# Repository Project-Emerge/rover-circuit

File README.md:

# Dropbot Circuit Board

## Scope of the Board

The Rover Circuit is a comprehensive controller board designed for robotics applications, specifically targeted at robot rovers. A key goal of this project is to make swarm robotics accessible to students, educators, and researchers, providing an affordable and easy-to-use platform for experimenting with multi-agent systems and decentralized control. 

It integrates dual-motor driving capabilities, 2-cell Li-ion battery management with USB-C charging, and provides multiple power domains (3.3V, 5V, 6V) for logic, sensors, and external compute modules like a Raspberry Pi. The board includes I2C and GPIO interfaces to facilitate communication with various sensors and control systems, making it a compact, all-in-one hardware platform for mobile robot development.

## Main Components & Features

* **Espressif ESP32-C6 (Microcontroller)**: The core processing unit of the board, offering Wi-Fi 6, Bluetooth LE, and IEEE 802.15.4 (Zigbee/Thread) connectivity. Its robust wireless capabilities are ideal for inter-robot communication in a swarm network.
* **Decawave DWM1000 (UWB Module)**: An Ultra-Wideband transceiver module designed for precise indoor localization, spatial awareness, and ranging between rovers. Crucial for coordinated swarm movements and mapping.
* **9-DOF Inertial Measurement Unit (IMU)**: 
  * *Bosch BMI270*: A 6-axis accelerometer and gyroscope for tracking movement and rotation.
  * *MEMSIC MMC5983MA*: A high-precision 3-axis magnetometer acting as a digital compass for absolute heading orientation.
* **TI BQ25887 (Battery Management)**: A 2-cell Li-ion boost-mode battery charger with integrated cell balancing and USB-C input support. It handles safe charging and power management for the entire rover.
* **TI DRV8833 (Motor Driver)**: A dual H-bridge motor driver capable of delivering 1.5A RMS per bridge. It is used to independently drive two DC motors (such as N20 motors) for locomotion.
* **STM6601 (Power Controller)**: A smart push-button on/off controller for robust hardware power management and user interaction.
* **Power Distribution System**: Dedicated voltage regulators generating 3.3V for internal logic and sensors, 6V for the motors, and a clean 5V output.
* **SBC Expansion & User Interface**: An expansion header capable of powering and interfacing with a Single Board Computer (e.g., Raspberry Pi) over 5V, along with a dedicated I2C connector for attaching an OLED display module.

These components work together to provide a complete, robust sensing, processing, and locomotion backend, allowing developers to focus on high-level swarm robotics software and decentralized algorithms without worrying about hardware integration.

## Sponsors

---

## License

MIT License - see LICENSE file for details.

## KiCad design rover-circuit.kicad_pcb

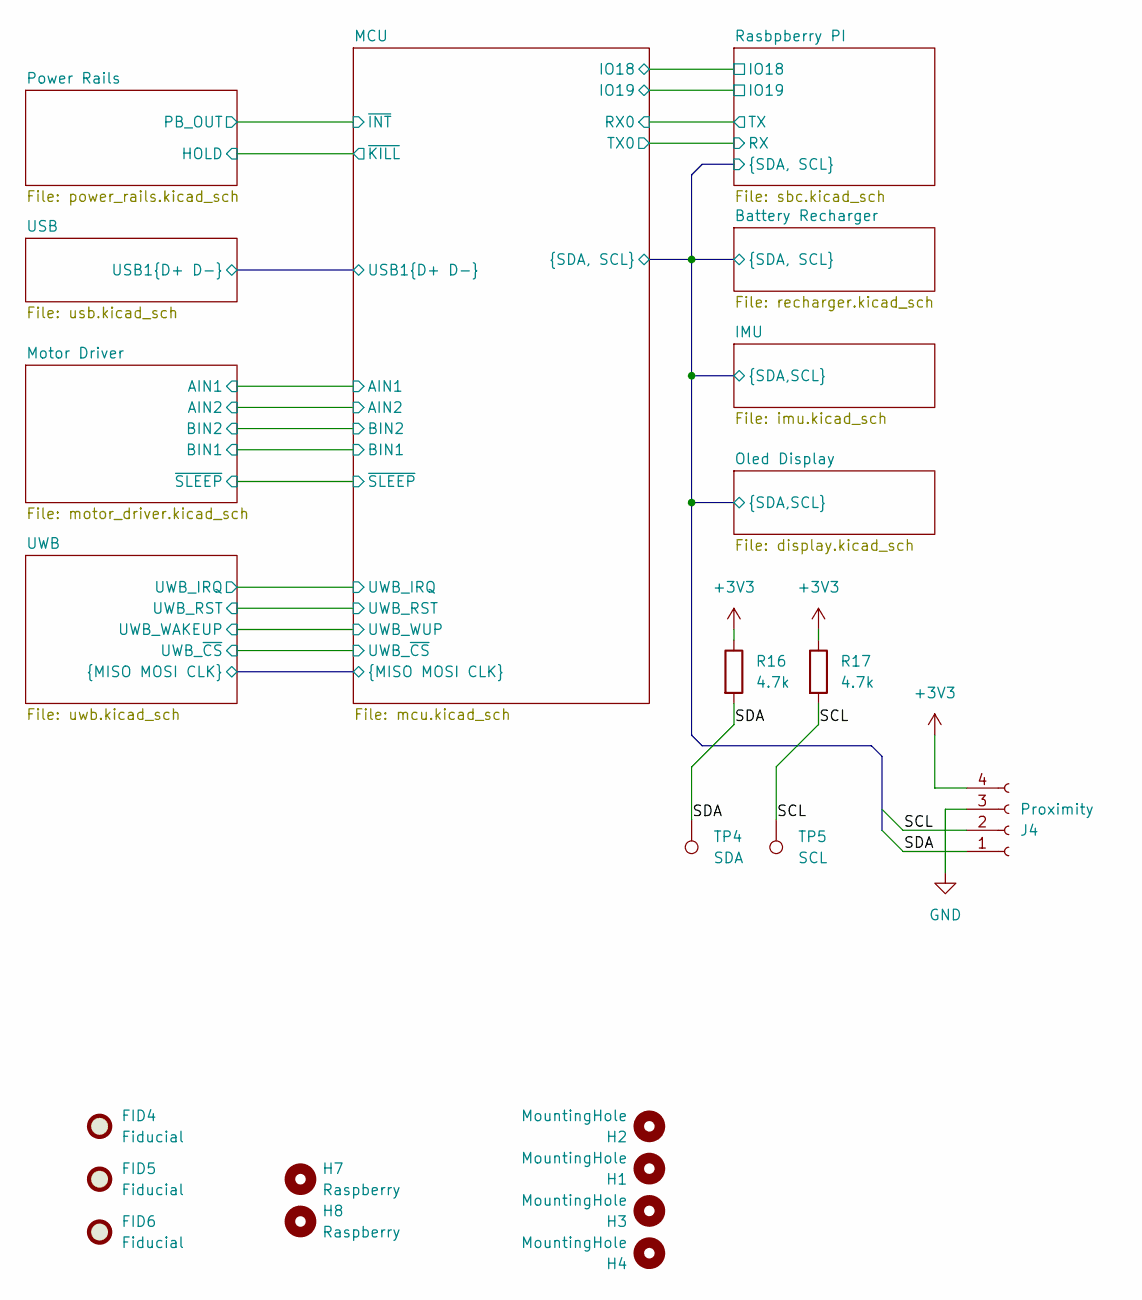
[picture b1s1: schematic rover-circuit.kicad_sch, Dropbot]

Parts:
FID4, FID5, FID6: Fiducial; Fiducial_0.5mm_Mask1mm
H1, H2, H3, H4: MountingHole; MountingHole_2.2mm_M2
H7, H8: Raspberry; MountingHole_2.5mm
J4: Proximity; JST_PH_S4B-PH-SM4-TB_1x04-1MP_P2.00mm_Horizontal; MPN S4B-PH-SM4-TB(LF)(SN); LCSC C265102
R16, R17: 4.7k; R_0603_1608Metric; MPN GPR060347; LCSC C25999
TP4: SDA; TestPoint_Pad_D1.0mm
TP5: SCL; TestPoint_Pad_D1.0mm

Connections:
+3V3: J4.4, R16.1, R17.1; also elsewhere on the board
/Battery Recharger/SCL: J4.2, R17.2, TP5.1 (1_1); also elsewhere on the board
/Battery Recharger/SDA: J4.1, R16.2, TP4.1 (1_1); also elsewhere on the board
GND: J4.3; also elsewhere on the board

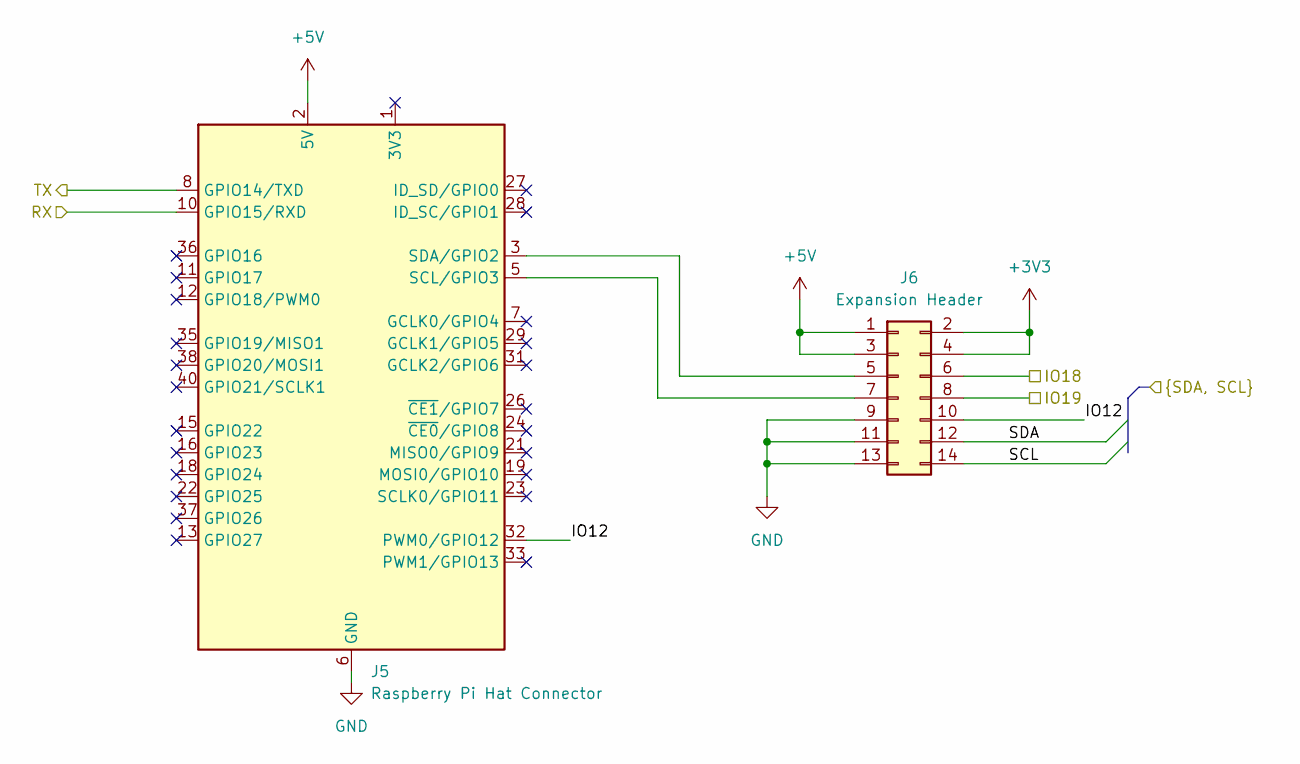
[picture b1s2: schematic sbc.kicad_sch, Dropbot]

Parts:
J5: Raspberry Pi Hat Connector; PinSocket_2x20_P2.54mm_Vertical_SMD; MPN 953240-2000-AR-PR; LCSC C22436166
J6: Expansion Header; PinHeader_2x07_P2.54mm_Vertical; MPN 61201421621; LCSC C492424

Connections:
+3V3: J6.2, J6.4; also elsewhere on the board
+5V: J5.2 (5V), J5.4 (5V), J6.1, J6.3; also elsewhere on the board
/Battery Recharger/SCL: J6.14; also elsewhere on the board
/Battery Recharger/SDA: J6.12; also elsewhere on the board
/MCU/IO18: J6.6; also elsewhere on the board
/MCU/IO19: J6.8; also elsewhere on the board
/MCU/RX0: J5.8 (GPIO14/TXD); also elsewhere on the board
/MCU/TX0: J5.10 (GPIO15/RXD); also elsewhere on the board
/Rasbpberry PI/IO12: J5.32 (PWM0/GPIO12), J6.10
GND: J5.6 (GND), J5.9 (GND), J5.14 (GND), J5.20 (GND), J5.25 (GND), J5.30 (GND), J5.34 (GND), J5.39 (GND), J6.9, J6.11, J6.13; also elsewhere on the board
unnamed: J5.5 (SCL/GPIO3), J6.7
unnamed: J5.3 (SDA/GPIO2), J6.5

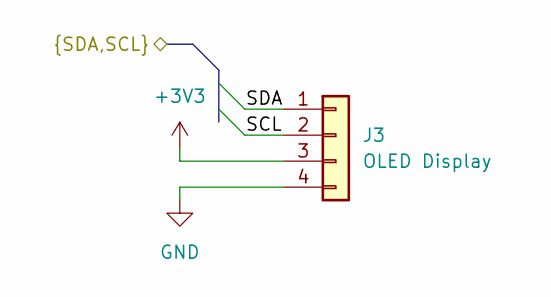
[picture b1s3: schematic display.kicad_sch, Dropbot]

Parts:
J3: OLED Display; PinSocket_1x04_P2.54mm_Vertical; MPN PPTC041LFBN-RC; LCSC C2718488

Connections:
+3V3: J3.3; also elsewhere on the board
/Battery Recharger/SCL: J3.2; also elsewhere on the board
/Battery Recharger/SDA: J3.1; also elsewhere on the board
GND: J3.4; also elsewhere on the board

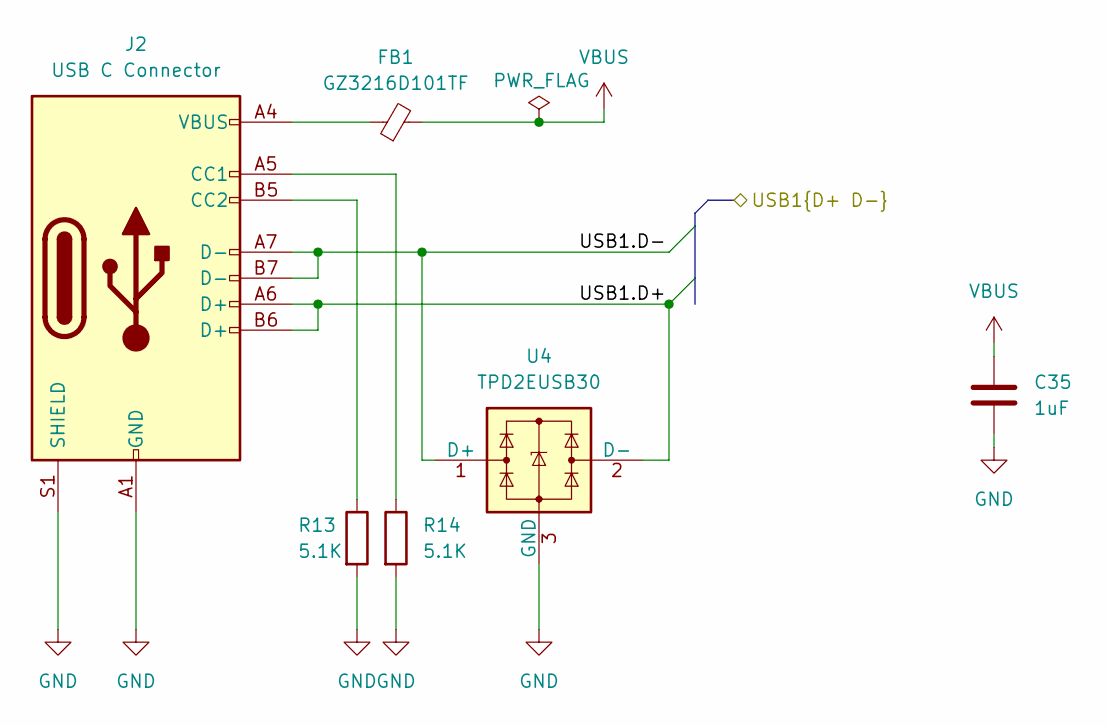
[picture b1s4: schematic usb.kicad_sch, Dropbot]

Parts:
C35: 1uF; C_0603_1608Metric; MPN GPC0603105; LCSC C5673
FB1: GZ3216D101TF; L_1206_3216Metric; MPN BLM31PG500SN1L; LCSC C369799
J2: USB C Connector; USB_C_Receptacle_G-Switch_GT-USB-7010ASV; MPN GT-USB-7010ASV; LCSC C2988369
R13, R14: 5.1K; R_0402_1005Metric; MPN GPR040251; LCSC C25905
U4: TPD2EUSB30; Texas_DRT-3; MPN TPD2EUSB30ADRTR; LCSC C94934

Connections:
/MCU/USB1.D+: J2.A6 (D+), J2.B6 (D+), U4.2 (D-); also elsewhere on the board
/MCU/USB1.D-: J2.A7 (D-), J2.B7 (D-), U4.1 (D+); also elsewhere on the board
GND: C35.2, J2.A1 (GND), J2.A12 (GND), J2.B1 (GND), J2.B12 (GND), J2.S1 (SHIELD), R13.2, R14.2, U4.3 (GND); also elsewhere on the board
unnamed: FB1.1, J2.A4 (VBUS), J2.A9 (VBUS), J2.B4 (VBUS), J2.B9 (VBUS)
unnamed: J2.A5 (CC1), R14.1
unnamed: J2.B5 (CC2), R13.1
VBUS: C35.1, FB1.2; also elsewhere on the board

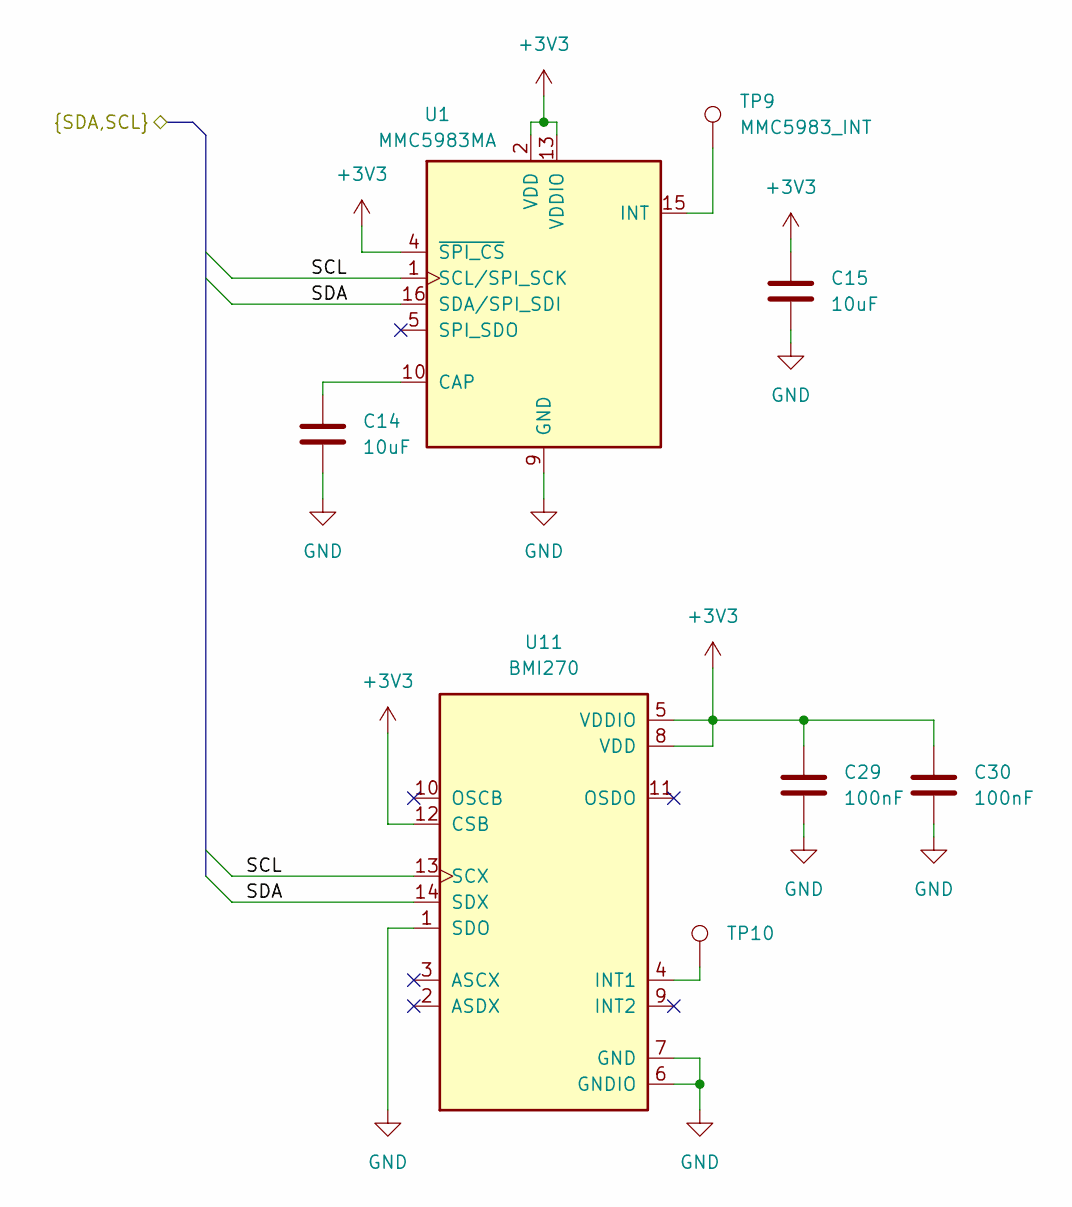
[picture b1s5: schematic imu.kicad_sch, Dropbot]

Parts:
C14, C15: 10uF; C_0603_1608Metric; MPN GPC0603106; LCSC C962136
C29, C30: 100nF; C_0603_1608Metric; MPN GPC0603104; LCSC C14663
TP9: MMC5983_INT; TestPoint_Pad_D1.0mm
TP10: INT1; TestPoint_Pad_D1.0mm
U1: MMC5983MA; LGA-16_3x3mm_P0.5mm; PARTREV A; LCSC C404329
U11: BMI270; Bosch_LGA-14_3x2.5mm_P0.5mm; MPN BMI270; LCSC C2836813

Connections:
+3V3: C15.1, C29.1, C30.1, U1.2 (VDD), U1.4 (~SPI_CS), U1.13 (VDDIO), U11.5 (VDDIO), U11.8 (VDD), U11.12 (CSB); also elsewhere on the board
/Battery Recharger/SCL: U1.1 (SCL/SPI_SCK), U11.13 (SCX); also elsewhere on the board
/Battery Recharger/SDA: U1.16 (SDA/SPI_SDI), U11.14 (SDX); also elsewhere on the board
GND: C14.2, C15.2, C29.2, C30.2, U1.9 (GND), U1.11 (GND), U11.1 (SDO), U11.6 (GNDIO), U11.7 (GND); also elsewhere on the board
unnamed: C14.1, U1.10 (CAP)
unnamed: TP9.1 (1_1), U1.15 (INT)
unnamed: TP10.1 (1_1), U11.4 (INT1)

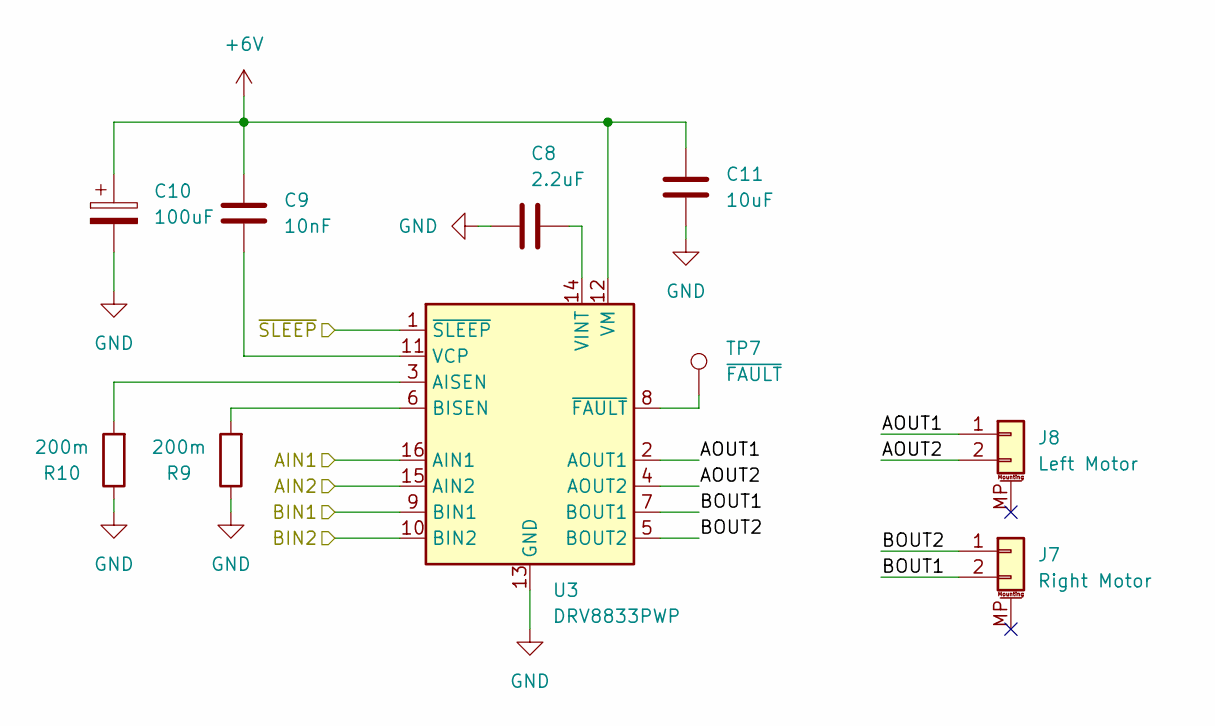
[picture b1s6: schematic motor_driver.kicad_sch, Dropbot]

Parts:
C8: 2.2uF; C_0603_1608Metric; MPN GPC0603225; LCSC C23630
C9: 10nF; C_0603_1608Metric; MPN GPC0603103; LCSC C1589
C10: 100uF; CP_Elec_6.3x5.4; MPN EEE-1CA101SP; LCSC C2887276
C11: 10uF; C_0805_2012Metric; MPN GPC0805106; LCSC C326595
J7: Right Motor; JST_PH_S2B-PH-SM4-TB_1x02-1MP_P2.00mm_Horizontal; MPN S2B-PH-SM4-TB(LF)(SN); LCSC C295747
J8: Left Motor; JST_PH_S2B-PH-SM4-TB_1x02-1MP_P2.00mm_Horizontal; MPN S2B-PH-SM4-TB(LF)(SN); LCSC C295747
R9, R10: 200m; R_1206_3216Metric; MPN ERJ-8BWFR200V; LCSC C5127778
TP7: ~{FAULT}; TestPoint_Pad_D1.0mm
U3: DRV8833PWP; HTSSOP-16-1EP_4.4x5mm_P0.65mm_EP3.4x5mm_Mask2.46x2.31mm_The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; MPN DRV8833PWPR; LCSC C50506

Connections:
+6V: C9.1, C10.1, C11.1, U3.12 (VM); also elsewhere on the board
/MCU/AIN1: U3.16 (AIN1); also elsewhere on the board
/MCU/AIN2: U3.15 (AIN2); also elsewhere on the board
/MCU/BIN1: U3.9 (BIN1); also elsewhere on the board
/MCU/BIN2: U3.10 (BIN2); also elsewhere on the board
/MCU/~SLEEP: U3.1 (~SLEEP); also elsewhere on the board
/Motor Driver/AOUT1: J8.1, U3.2 (AOUT1)
/Motor Driver/AOUT2: J8.2, U3.4 (AOUT2)
/Motor Driver/BOUT1: J7.2, U3.7 (BOUT1)
/Motor Driver/BOUT2: J7.1, U3.5 (BOUT2)
GND: C8.2, C10.2, C11.2, R9.1, R10.1, U3.13 (GND), U3.17 (GND); also elsewhere on the board
unnamed: R10.2, U3.3 (AISEN)
unnamed: R9.2, U3.6 (BISEN)
unnamed: C9.2, U3.11 (VCP)
unnamed: C8.1, U3.14 (VINT)
unnamed: TP7.1 (1_1), U3.8 (~FAULT)

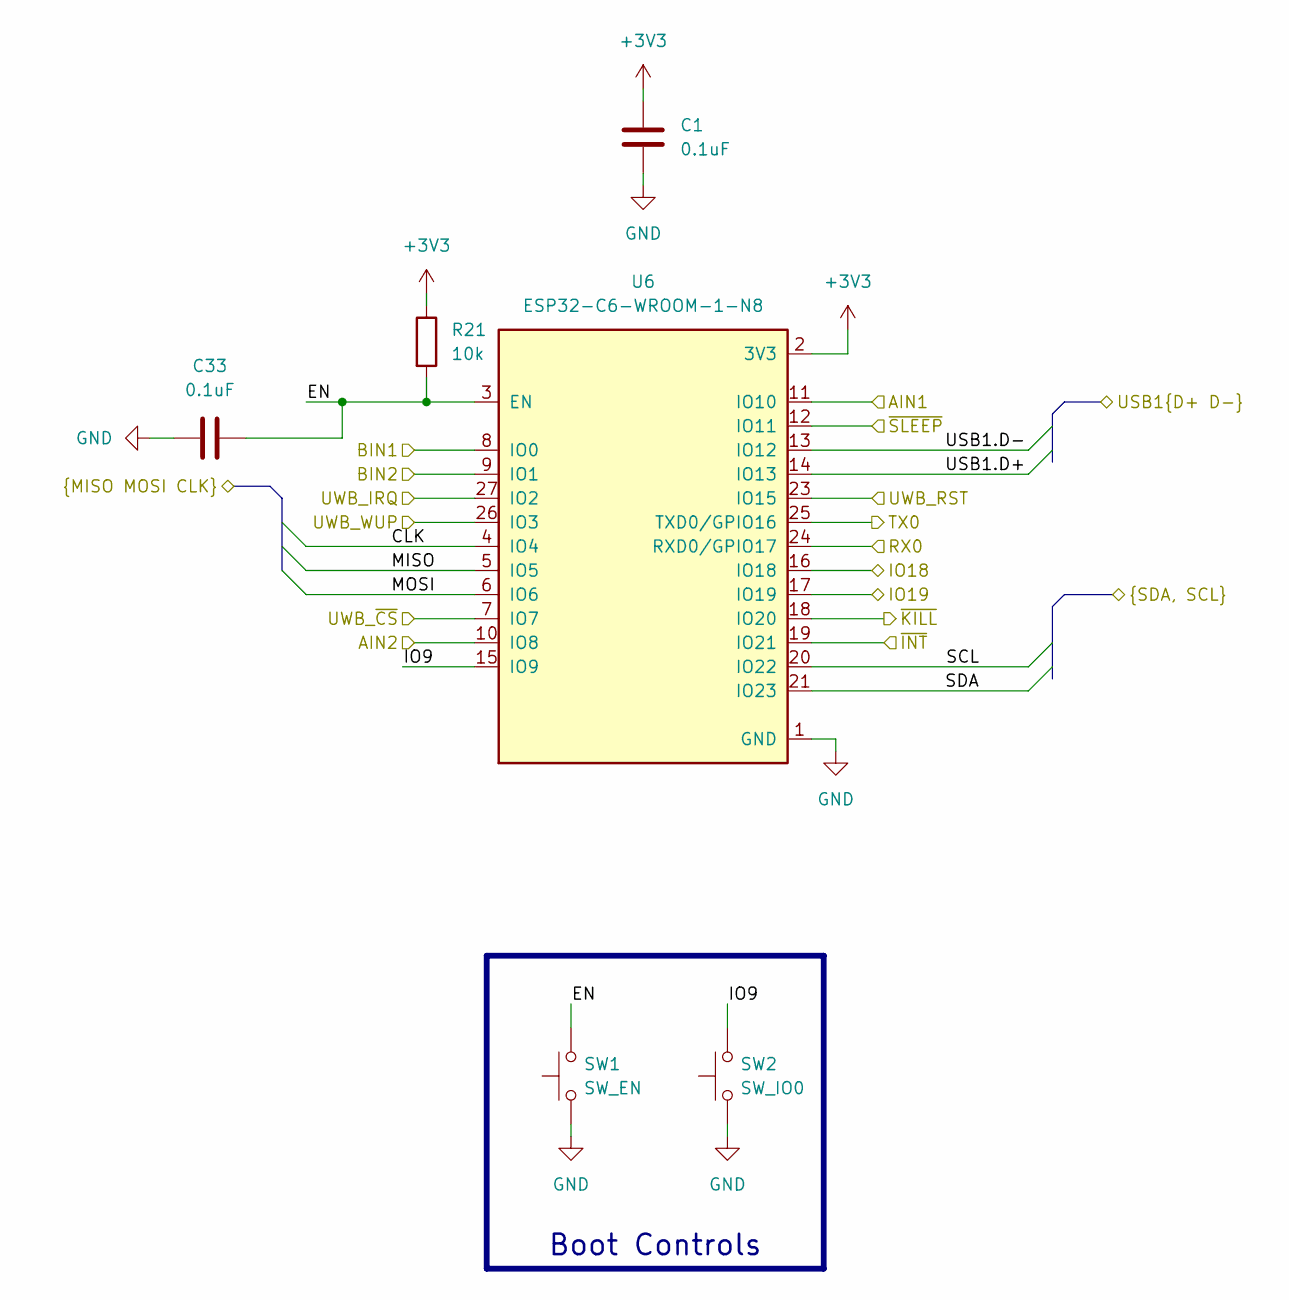
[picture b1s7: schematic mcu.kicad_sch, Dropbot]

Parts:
C1: 0.1uF; C_0805_2012Metric; LCSC C49678
C33: 0.1uF; C_0805_2012Metric; MPN GPC0805104; LCSC C49678
R21: 10k; R_0603_1608Metric; MPN GPR060310K; LCSC C15401
SW1: SW_EN; SW_SPST_B3U-1000P; MPN B3U-1000P; LCSC C231329
SW2: SW_IO0; SW_SPST_B3U-1000P; MPN B3U-1000P; LCSC C231329
U6: ESP32-C6-WROOM-1-N8; XCVR_ESP32-C6-WROOM-1-N8; PARTREV 1.0; LCSC C5366877

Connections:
+3V3: C1.1, R21.1, U6.2 (3V3); also elsewhere on the board
/Battery Recharger/SCL: U6.20 (IO22); also elsewhere on the board
/Battery Recharger/SDA: U6.21 (IO23); also elsewhere on the board
/MCU/AIN1: U6.11 (IO10); also elsewhere on the board
/MCU/AIN2: U6.10 (IO8); also elsewhere on the board
/MCU/BIN1: U6.8 (IO0); also elsewhere on the board
/MCU/BIN2: U6.9 (IO1); also elsewhere on the board
/MCU/CLK: U6.4 (IO4); also elsewhere on the board
/MCU/EN: C33.2, R21.2, SW1.2, U6.3 (EN)
/MCU/IO9: SW2.2, U6.15 (IO9)
/MCU/IO18: U6.16 (IO18); also elsewhere on the board
/MCU/IO19: U6.17 (IO19); also elsewhere on the board
/MCU/MISO: U6.5 (IO5); also elsewhere on the board
/MCU/MOSI: U6.6 (IO6); also elsewhere on the board
/MCU/RX0: U6.24 (RXD0/GPIO17); also elsewhere on the board
/MCU/TX0: U6.25 (TXD0/GPIO16); also elsewhere on the board
/MCU/USB1.D+: U6.14 (IO13); also elsewhere on the board
/MCU/USB1.D-: U6.13 (IO12); also elsewhere on the board
/MCU/UWB_IRQ: U6.27 (IO2); also elsewhere on the board
/MCU/UWB_RST: U6.23 (IO15); also elsewhere on the board
/MCU/UWB_WUP: U6.26 (IO3); also elsewhere on the board
/MCU/UWB_~CS: U6.7 (IO7); also elsewhere on the board
/MCU/~INT: U6.19 (IO21); also elsewhere on the board
/MCU/~KILL: U6.18 (IO20); also elsewhere on the board
/MCU/~SLEEP: U6.12 (IO11); also elsewhere on the board
GND: C1.2, C33.1, SW1.1, SW2.1, U6.1 (GND), U6.28 (GND), U6.29_1 (GND), U6.29_2 (GND), U6.29_3 (GND), U6.29_4 (GND), U6.29_5 (GND), U6.29_6 (GND), U6.29_7 (GND), U6.29_8 (GND), U6.29_9 (GND); also elsewhere on the board

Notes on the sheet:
Boot Controls

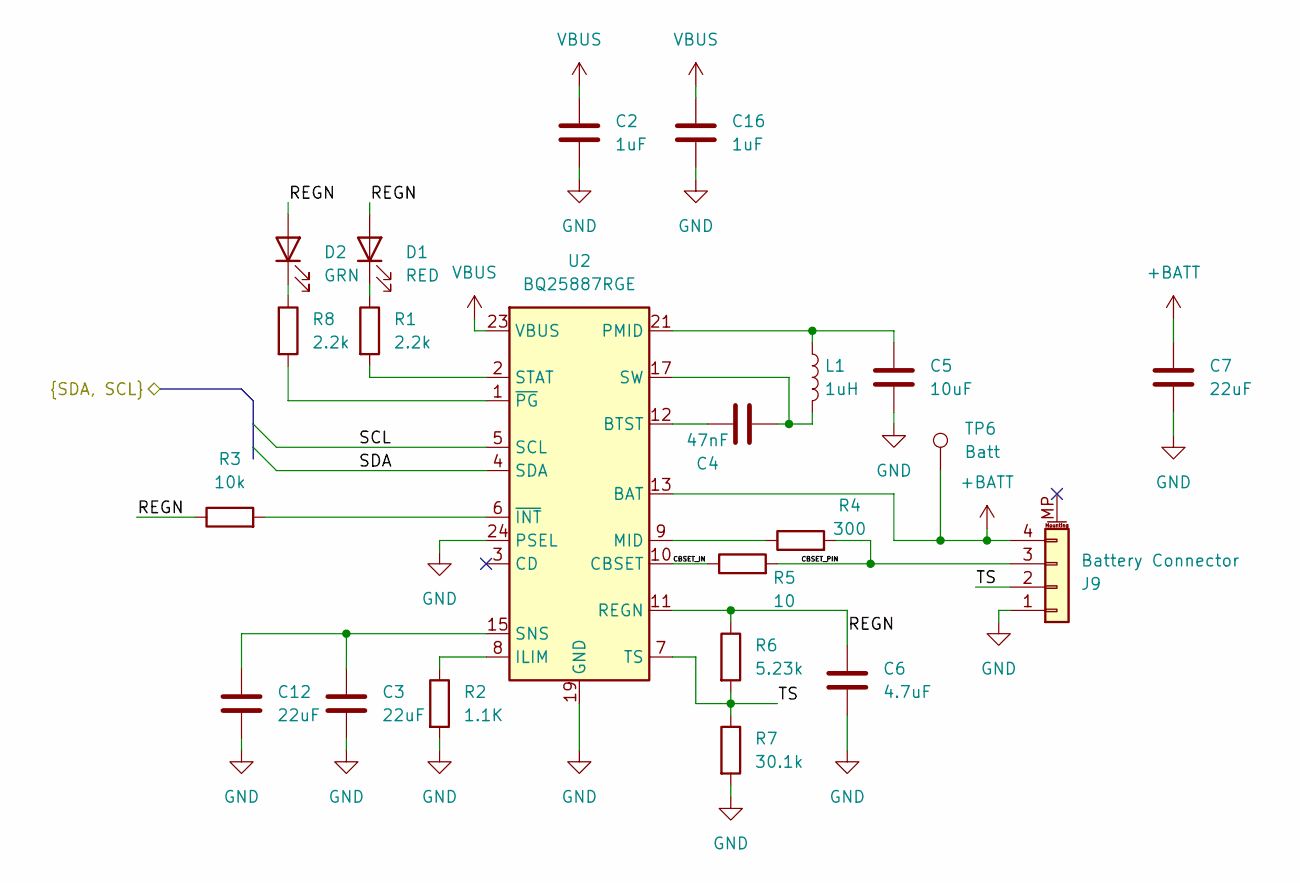
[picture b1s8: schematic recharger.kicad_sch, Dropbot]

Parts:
C2, C16: 1uF; C_0603_1608Metric; MPN GPC0603105; LCSC C5673
C3, C12: 22uF; C_1206_3216Metric; MPN GPC1206226; LCSC C53084537
C4: 47nF; C_0603_1608Metric; MPN GPC0603473; LCSC C1622
C5: 10uF; C_1206_3216Metric; MPN GPC1206106; LCSC C13585
C6: 4.7uF; C_0603_1608Metric; MPN GPC0603475; LCSC C69335
C7: 22uF; C_0603_1608Metric; MPN GRM188C61E226ME01D; LCSC C86295
D1: RED; LED_0603_1608Metric; MPN 150060RS75000; LCSC C2286
D2: GRN; LED_0603_1608Metric; MPN 150060VS75000; LCSC C965805
J9: Battery Connector; JST_PH_B4B-PH-SM4-TB_1x04-1MP_P2.00mm_Vertical; MPN B4B-PH-SM4-TB(LF)(SN); LCSC C160354
L1: 1uH; L_Sunlord_MWSA0518S; LCSC C475532
R1, R8: 2.2k; R_0603_1608Metric; MPN GPR060322; LCSC C4190
R2: 1.1K; R_0603_1608Metric; MPN GPR060311; LCSC C22764
R3: 10k; R_0603_1608Metric; MPN GPR060310K; LCSC C15401
R4: 300; R_0603_1608Metric; MPN GPR0603300R; LCSC C2930092
R5: 10; R_2512_6332Metric; MPN CRM2512-FX-10R0ELF; LCSC C840605
R6: 5.23k; R_0603_1608Metric; MPN GPR0603523; LCSC C23068
R7: 30.1k; R_0603_1608Metric; MPN GPR0603301; LCSC C23000
TP6: Batt; TestPoint_Pad_D1.0mm
U2: BQ25887RGE; Texas_RGE0024H_VQFN-24-1EP_4x4mm_P0.5mm_EP2.7x2.7mm; MPN BQ25887RGER; LCSC C2761614

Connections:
+BATT: C7.1, J9.4, TP6.1 (1_1), U2.13 (BAT), U2.14 (BAT); also elsewhere on the board
/Battery Recharger/CBSET_IN: R5.1, U2.10 (CBSET)
/Battery Recharger/CBSET_PIN: J9.3, R4.2, R5.2
/Battery Recharger/REGN: C6.1, D1.2 (A), D2.2 (A), R3.1, R6.1, U2.11 (REGN)
/Battery Recharger/SCL: U2.5 (SCL); also elsewhere on the board
/Battery Recharger/SDA: U2.4 (SDA); also elsewhere on the board
/Battery Recharger/TS: J9.2, R6.2, R7.1, U2.7 (TS)
GND: C2.2, C3.2, C5.2, C6.2, C7.2, C12.2, C16.2, J9.1, R2.2, R7.2, U2.19 (GND), U2.20 (GND), U2.24 (PSEL), U2.25 (GND); also elsewhere on the board
unnamed: C4.1, L1.2, U2.17 (SW), U2.18 (SW)
unnamed: C5.1, L1.1, U2.21 (PMID), U2.22 (PMID)
unnamed: C3.1, C12.1, U2.15 (SNS), U2.16 (SNS)
unnamed: D1.1 (K), R1.1
unnamed: D2.1 (K), R8.1
unnamed: C4.2, U2.12 (BTST)
unnamed: R2.1, U2.8 (ILIM)
unnamed: R4.1, U2.9 (MID)
unnamed: R1.2, U2.2 (STAT)
unnamed: R3.2, U2.6 (~INT)
unnamed: R8.2, U2.1 (~PG)
VBUS: C2.1, C16.1, U2.23 (VBUS); also elsewhere on the board

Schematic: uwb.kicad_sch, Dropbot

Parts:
C27: 0.1uF; C_0805_2012Metric; MPN GPC0805104; LCSC C49678
D5, D6: BLUE; LED_0603_1608Metric; MPN 150060BS75000; LCSC C965807
DWM1: DWM1000; MPN DWM1000
R18: 10k; R_0603_1608Metric; MPN GPR060310K; LCSC C15401
R19, R20: 470; R_0603_1608Metric; MPN GPR0603470R; LCSC C23179

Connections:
+3V3: C27.1, DWM1.5 (VDDAON), DWM1.6 (VDD3V3), DWM1.7 (VDD3V3); also elsewhere on the board
/MCU/CLK: DWM1.20 (SPICLK); also elsewhere on the board
/MCU/MISO: DWM1.19 (SPIMISO); also elsewhere on the board
/MCU/MOSI: DWM1.18 (SPIMOSI); also elsewhere on the board
/MCU/UWB_IRQ: DWM1.22 (IRQ/GPIO8), R18.1; also elsewhere on the board
/MCU/UWB_RST: DWM1.3 (~RST); also elsewhere on the board
/MCU/UWB_WUP: DWM1.2 (WAKEUP); also elsewhere on the board
/MCU/UWB_~CS: DWM1.17 (~SPICS); also elsewhere on the board
GND: C27.2, D5.1 (K), D6.1 (K), DWM1.8 (VSS), DWM1.16 (VSS), DWM1.21 (VSS), DWM1.23 (VSS), DWM1.24 (VSS), R18.2; also elsewhere on the board
unnamed: D5.2 (A), R19.2
unnamed: D6.2 (A), R20.2
unnamed: DWM1.13 (GPIO2/RXLED), R19.1
unnamed: DWM1.12 (GPIO3/TXLED), R20.1

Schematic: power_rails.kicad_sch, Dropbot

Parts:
C13, C19: 100nF; C_0603_1608Metric; MPN GPC0603104; LCSC C14663
C17, C20, C21, C23, C24, C28: 22uF; C_0805_2012Metric; MPN GPC0805226; LCSC C296720
C18, C22, C25: 10uF; C_0805_2012Metric; MPN GPC0805106; LCSC C326595
C26: 2.2uF; C_0603_1608Metric; MPN GPC0603225; LCSC C415535
C31: 1uF; C_0603_1608Metric; MPN GPC0603105; LCSC C5360793
C32: 1uF; C_0603_1608Metric; MPN GPC0603105; LCSC C5673
C34: 470nF; C_0603_1608Metric; LCSC C1623
D3: LED; LED_0603_1608Metric; MPN 150060RS75000; LCSC C2286
L2: 2.2uH; L_Coilcraft_LPS3010; MPN LPS3015-222MRC; LCSC C2844756
L3: 4.7uH; L_Chilisin_BWVS00505030; MPN LVS505040-4R7M-N; LCSC C108284
L4: 10uH; L_Sunlord_MWSA0503S; LCSC C408412
R11: 64.9k; R_0603_1608Metric; MPN GPR0603649; LCSC C14891
R12: 10k; R_0603_1608Metric; MPN GPR060310K; LCSC C15401
R15: 100K; R_0603_1608Metric; MPN GPR0603100K; LCSC C25803
SW3: ~{SR}; SW_SPST_B3U-1000P; MPN B3U-1000P; LCSC C231329
SW4: ~{PB}; SW_SPST_B3U-1000P; MPN B3U-1000P; LCSC C231329
TP1: 3V3 TP; TestPoint_Pad_D1.0mm
TP2: 5V TP; TestPoint_Pad_D1.0mm
TP3: 6V TP; TestPoint_Pad_D1.0mm
U5: AP63200WU; TSOT-23-6; MPN AP63200WU-7; LCSC C2071868
U7: AP63205WU; TSOT-23-6; MPN AP63205WU-7; LCSC C2071056
U8: STM6601CM2DDM6F; TDFN-12_2x3mm_P0.5mm; MPN STM6601CM2DDM6F; LCSC C155599
U9: TPS62162DSG; WSON-8-1EP_2x2mm_P0.5mm_EP0.9x1.6mm_ThermalVias; MPN TPS62162DSGR; LCSC C40256
U12: MCP1799T-5002H/TT; SOT-23; MPN MCP1799T-5002H/TT; LCSC C2890492

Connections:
+3V3: C17.1, C28.1, L2.2, R15.1, TP1.1 (1_1), U9.5 (FB), U9.6 (VOS); also elsewhere on the board
+5V: C20.1, C21.1, L3.2, TP2.1 (1_1), U7.1 (FB); also elsewhere on the board
+6V: C23.1, C24.1, L4.2, R11.1, TP3.1 (1_1); also elsewhere on the board
+BATT: C18.1, C22.1, C25.1, C31.1, U5.3 (IN), U7.3 (IN), U9.2 (VIN), U12.3 (VI); also elsewhere on the board
/MCU/~INT: U8.8 (~PB_OUT); also elsewhere on the board
/MCU/~KILL: U8.4 (PS_HOLD); also elsewhere on the board
/Power Rails/STM6601_EN: U5.2 (EN), U7.2 (EN), U8.9 (~EN/EN), U9.3 (EN)
GND: C17.2, C18.2, C20.2, C21.2, C22.2, C23.2, C24.2, C25.2, C26.2, C28.2, C31.2, C32.2, C34.2, R12.2, SW3.1, SW4.1, U5.4 (GND), U7.4 (GND), U8.12 (GND), U9.1 (PGND), U9.4 (AGND), U9.9 (PAD), U12.1 (GND); also elsewhere on the board
unnamed: D3.2 (A), R15.2
unnamed: D3.1 (K), U9.8 (PG)
unnamed: C13.1, U5.6 (BST)
unnamed: R11.2, R12.1, U5.1 (FB)
unnamed: C13.2, L4.1, U5.5 (SW)
unnamed: C19.1, U7.6 (BST)
unnamed: C19.2, L3.1, U7.5 (SW)
unnamed: C34.1, U8.5 (C_SRD)
unnamed: C32.1, U8.3 (Vref)
unnamed: SW4.2, U8.6 (~PB)
unnamed: SW3.2, U8.2 (~SR)
unnamed: L2.1, U9.7 (SW)
unnamed: C26.1, U8.1 (Vcc), U12.2 (VO)

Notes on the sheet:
6V Motor Rail
3V3 Rail
5V Rail
